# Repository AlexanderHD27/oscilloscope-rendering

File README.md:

# Oscilloscope Drawing

A device that draws on an oscilloscope.

## Introduction
Drawing on analog oscilloscope is almost a classic in the electronics/microcontroller community now.
This is done by setting the scope to XY-Mode and then controlling the X/Y-deflection of the electron-beam. My Scope has no Z-Channel. I cannot control the intensity of beam (or switches off) by voltage yet

This Project is my shot at this. I use custom hardware (build on perf-board) to archive this goal. I have build
a 2-Channel 16bit DAC with an refresh rate of around 1 MSample per second. Further more a usb-interface + driver shall be developed.

My current todo list can be found [here](TODO.md)

### Hardware

Everything is solder onto pref-boards an connected via pin-headers and jumpers

(Diagram of the System-Hardware components)

The DACs are R-2R-Ladder DAC on a made custom PCB. The Input-Bits are feed from Octal-D-Latches ([74HC573](https://www.reichelt.de/oktal-d-type-latch-3-state-2--6-v-dil-20-74hc-573-p3264.html?search=74HC573)) in combination with some other logic ICs to reduce pin usage on the RPi Pico. Data sent via a 8-bit a parallel Bus to

<br>

At 1 MHz Square Wave, the analog output signal quality is significantly degraded. Testing revealed that probably R-2R_Ladder DAC is the weak link and needs further improvement. I currently use R = 11kOhm.

Yellow: X-Channel, Blue: Y-Channel, Magenta: Digital Input Signal to the DAC. (Yellow and Blue are coupled to AC, they usually to remove the 2.5V offset)

For testing the optics I did use a Hameg MH 312 Oscilloscope (I got this one used from Kleinanzeigen, so its already falling apart: semi-broken Coupling-switch, not being able focus the beam correctly, X-Pos nob falling off all the time)

### Further Components
- [Firmware](./firmware/README.md): Documentation is done by [doxygen](https://www.mintcalc.com/projects/osci-rendering/docs/index.html)

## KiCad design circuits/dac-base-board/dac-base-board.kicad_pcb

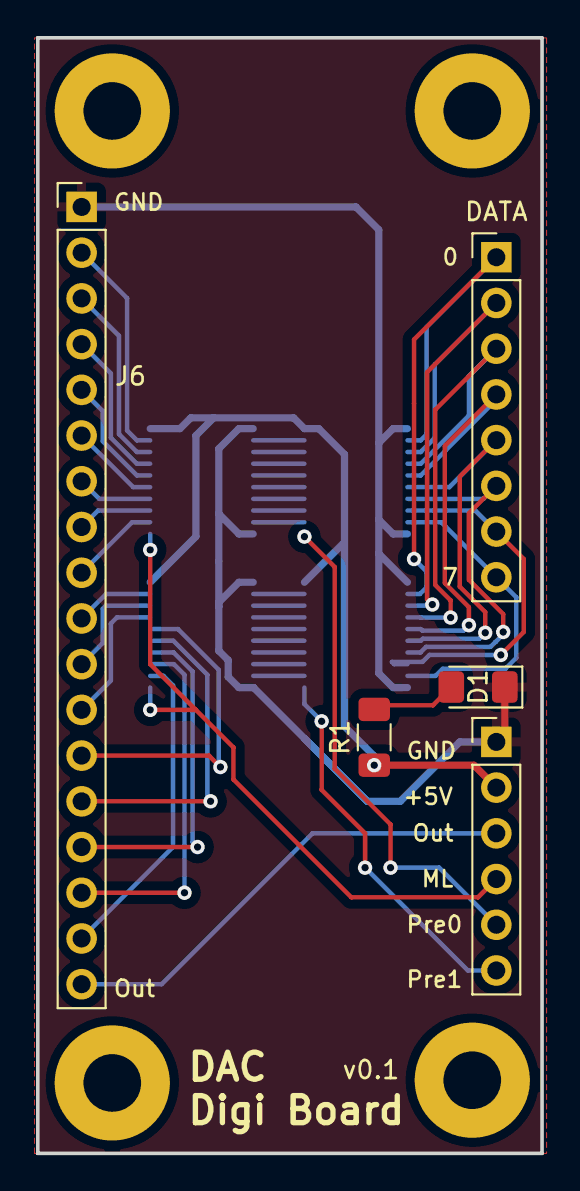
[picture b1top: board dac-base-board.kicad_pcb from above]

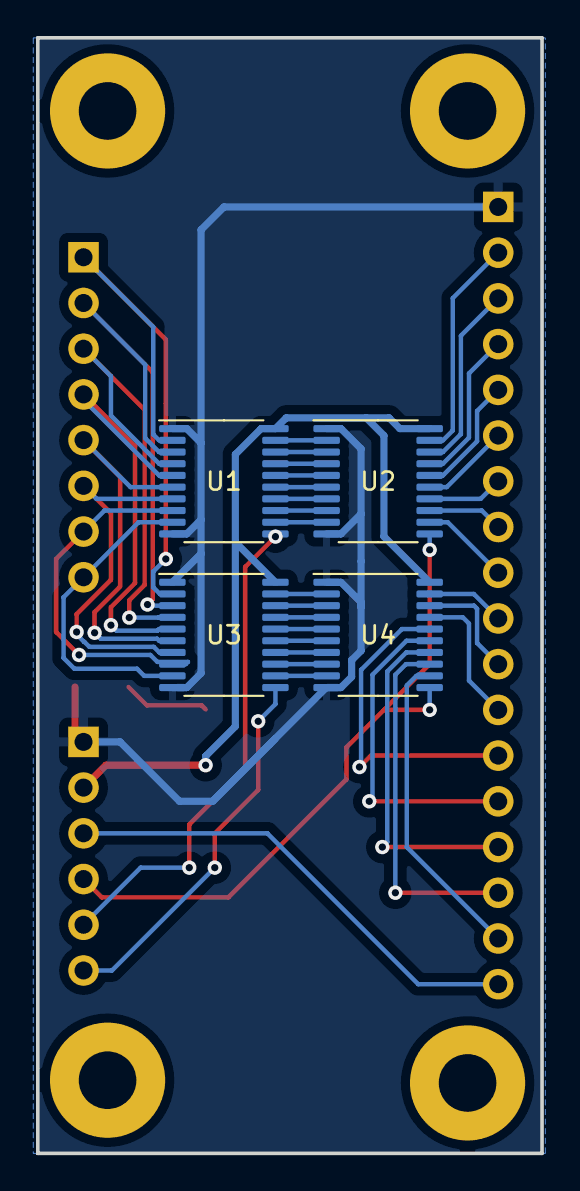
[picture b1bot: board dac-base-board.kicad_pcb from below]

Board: 2 copper layers, 28.0 x 62.0 mm, 12 parts (4 on the bottom side), 47 nets.

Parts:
D1: LED; LED_1206_3216Metric_Pad1.42x1.75mm_HandSolder
DATA: Data; PinHeader_1x08_P2.54mm_Vertical
J1: Conn; PinHeader_1x06_P2.54mm_Vertical
J6: DAC X; PinHeader_1x18_P2.54mm_Vertical
R1: 220; R_1206_3216Metric_Pad1.30x1.75mm_HandSolder
REF: MountingHole_3.2mm_M3_Pad
REF#2, REF#3: MountingHole_3.2mm_M3_Pad
U1, U2, U3, U4: 74LS573; TSSOP-20_4.4x6.5mm_P0.65mm

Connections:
+5V: J1.2, R1.2, U1.20 (VCC), U2.20 (VCC), U3.20 (VCC), U4.20 (VCC)
/D0: DATA.1, U1.2 (D0), U3.2 (D0)
/D1: DATA.2, U1.3 (D1), U3.3 (D1)
/D2: DATA.3, U1.4 (D2), U3.4 (D2)
/D3: DATA.4, U1.5 (D3), U3.5 (D3)
/D4: DATA.5, U1.6 (D4), U3.6 (D4)
/D5: DATA.6, U1.7 (D5), U3.7 (D5)
/D6: DATA.7, U1.8 (D6), U3.8 (D6)
/D7: DATA.8, U1.9 (D7), U3.9 (D7)
/DAC_D0: J6.2, U2.19 (Q0)
/DAC_D1: J6.3, U2.18 (Q1)
/DAC_D2: J6.4, U2.17 (Q2)
/DAC_D3: J6.5, U2.16 (Q3)
/DAC_D4: J6.6, U2.15 (Q4)
/DAC_D5: J6.7, U2.14 (Q5)
/DAC_D6: J6.8, U2.13 (Q6)
/DAC_D7: J6.9, U2.12 (Q7)
/DAC_D8: J6.10, U4.19 (Q0)
/DAC_D9: J6.11, U4.18 (Q1)
/DAC_D10: J6.12, U4.17 (Q2)
/DAC_D11: J6.13, U4.16 (Q3)
/DAC_D12: J6.14, U4.15 (Q4)
/DAC_D13: J6.15, U4.14 (Q5)
/DAC_D14: J6.16, U4.13 (Q6)
/DAC_D15: J6.17, U4.12 (Q7)
/Master_Load: J1.4, U2.11 (Load), U4.11 (Load)
/OUT: J1.3, J6.18
/Pre0: J1.5, U1.11 (Load)
/Pre1: J1.6, U3.11 (Load)
GND: D1.1 (K), J1.1, J6.1, U1.1 (OE), U1.10 (GND), U2.1 (OE), U2.10 (GND), U3.1 (OE), U3.10 (GND), U4.1 (OE), U4.10 (GND)
unnamed: D1.2 (A), R1.1
unnamed: U1.19 (Q0), U2.2 (D0)
unnamed: U1.18 (Q1), U2.3 (D1)
unnamed: U1.17 (Q2), U2.4 (D2)
unnamed: U1.16 (Q3), U2.5 (D3)
unnamed: U1.15 (Q4), U2.6 (D4)
unnamed: U1.14 (Q5), U2.7 (D5)
unnamed: U1.13 (Q6), U2.8 (D6)
unnamed: U1.12 (Q7), U2.9 (D7)
unnamed: U3.19 (Q0), U4.2 (D0)
unnamed: U3.18 (Q1), U4.3 (D1)
unnamed: U3.17 (Q2), U4.4 (D2)
unnamed: U3.16 (Q3), U4.5 (D3)
unnamed: U3.15 (Q4), U4.6 (D4)
unnamed: U3.14 (Q5), U4.7 (D5)
unnamed: U3.13 (Q6), U4.8 (D6)
unnamed: U3.12 (Q7), U4.9 (D7)

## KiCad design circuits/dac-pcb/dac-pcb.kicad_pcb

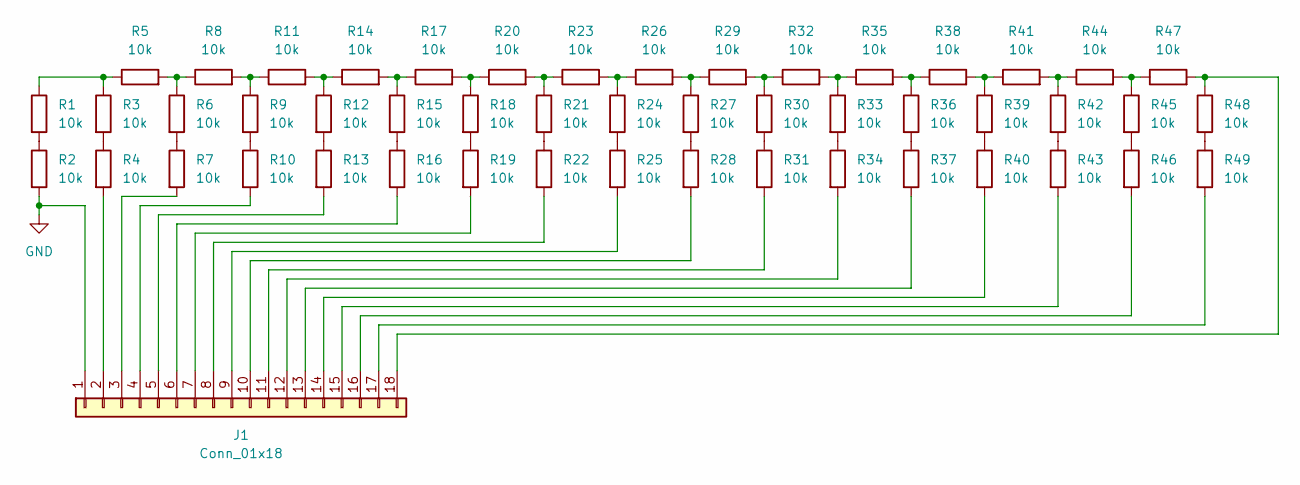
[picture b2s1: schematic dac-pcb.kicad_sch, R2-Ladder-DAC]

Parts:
J1: Conn_01x18; PinHeader_1x18_P2.54mm_Horizontal
R1, R2, R3, R4, R5, R6, R7, R8, R9, R10, R11, R12, R13, R14, R15, R16, R17, R18, R19, R20, R21, R22, R23, R24, R25, R26, R27, R28, R29, R30, R31, R32, R33, R34, R35, R36, R37, R38, R39, R40, R41, R42, R43, R44, R45, R46, R47, R48, R49: 10k; R_1206_3216Metric

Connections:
GND: J1.1, R2.2
unnamed: J1.2, R4.2
unnamed: J1.3, R7.2
unnamed: J1.4, R10.2
unnamed: J1.5, R13.2
unnamed: J1.6, R16.2
unnamed: J1.7, R19.2
unnamed: J1.8, R22.2
unnamed: J1.9, R25.2
unnamed: J1.10, R28.2
unnamed: J1.11, R31.2
unnamed: J1.12, R34.2
unnamed: J1.13, R37.2
unnamed: J1.14, R40.2
unnamed: J1.15, R43.2
unnamed: J1.16, R46.2
unnamed: J1.17, R49.2
unnamed: J1.18, R47.2, R48.1
unnamed: R1.1, R3.1, R5.1
unnamed: R1.2, R2.1
unnamed: R3.2, R4.1
unnamed: R5.2, R6.1, R8.1
unnamed: R6.2, R7.1
unnamed: R9.2, R10.1
unnamed: R8.2, R9.1, R11.1
unnamed: R11.2, R12.1, R14.1
unnamed: R12.2, R13.1
unnamed: R14.2, R15.1, R17.1
unnamed: R15.2, R16.1
unnamed: R17.2, R18.1, R20.1
unnamed: R18.2, R19.1
unnamed: R20.2, R21.1, R23.1
unnamed: R21.2, R22.1
unnamed: R23.2, R24.1, R26.1
unnamed: R24.2, R25.1
unnamed: R26.2, R27.1, R29.1
unnamed: R27.2, R28.1
unnamed: R29.2, R30.1, R32.1
unnamed: R30.2, R31.1
unnamed: R32.2, R33.1, R35.1
unnamed: R33.2, R34.1
unnamed: R35.2, R36.1, R38.1
unnamed: R36.2, R37.1
unnamed: R38.2, R39.1, R41.1
unnamed: R39.2, R40.1
unnamed: R41.2, R42.1, R44.1
unnamed: R42.2, R43.1
unnamed: R44.2, R45.1, R47.1
unnamed: R45.2, R46.1
unnamed: R48.2, R49.1

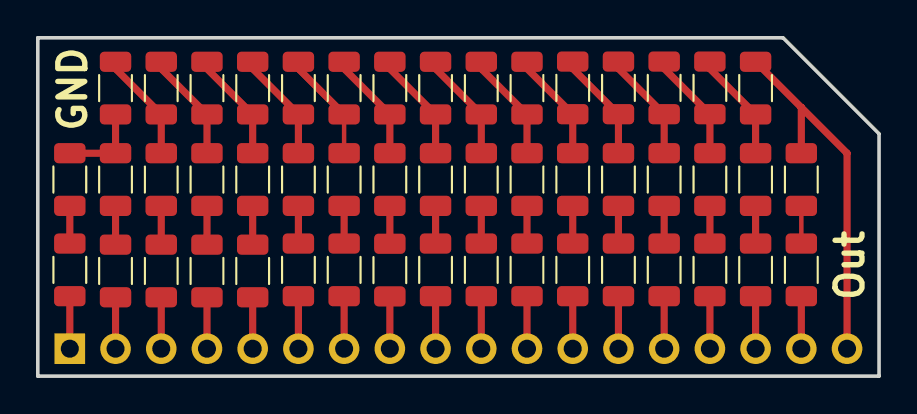
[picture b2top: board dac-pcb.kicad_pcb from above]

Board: 2 copper layers, 46.7 x 18.8 mm, 50 parts (1 on the bottom side), 50 nets.

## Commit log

2024-02-09 Added README + some doc images + SystemSchematic
2024-02-09 Added basic firmware to repo
2024-02-09 Added DAC-pcb
2024-02-09 Added PCB Manfucaturer to README
2024-02-10 Added USB test file/project to CMake & DevEnv
2024-02-10 Add tinyusb
2024-02-10 removed symlinks of example_auto_set_url.cmake and pico_sdk_import.cmake
2024-02-10 Update README.md with link to dac-pcb prod-file
2024-02-10 Fixed missing label in HardwareSystemDiagram
2024-02-10 Change PICO sdk to workspace-local sdk
2024-02-10 Got Pico SDK example of USB to work
2024-02-10 Cleaned up DAC code and separated it into folder
2024-02-11 Implemented basic generators
2024-02-11 Added squares.jpeg
2024-02-11 Update README.md with a small todo list
2024-02-11 Create Flow-Chart for Job System
2024-02-11 Fixed Problem with second core not starting after reset via openocd
2024-02-12 Added FreeRTOS to project
2024-02-12 Created flow-chart for new queue-based dataflow
2024-02-12 FlowChart: Updated some stuff and added task names
2024-02-12 Implemented queue base system
2024-02-12 Found Deadlock Issue
2024-02-12 Fixed deadlock issue by removing jobs queue and implemented frame-repeat
2024-02-12 Change buffer miss to check next cycle (instead of next frame repeat cycle)
2024-02-12 Reorganized Docs and updated README
2024-02-12 Update README.md inserted missing new line
2024-02-12 Create Instruction Parsing + Generation of NONE, CONST and LINE
2024-02-13 Implement cubic generation for floats and fixpoint
2024-02-13 Fixed bug in parameter reading
2024-02-13 Updated FreeRTOS-Kernel
2024-02-13 Implemented Qubic Curves
2024-02-14 Implemented Fixpoint taylor series for sin
2024-02-14 Fixed skipped samples by Invalid Offset
2024-02-14 built small sin&cos demo
2024-02-14 Added Demo of rendering sine
2024-02-14 Squashed commit of the following:
    commit 72b70e328290417968875a4158c1d6cbc331ddba
    Author: alexander <alexander@hal>
    Date: Wed Feb 14 22:44:02 2024 +0100
    Added Demo of rendering sine
    commit 6b187587fa563b0e1b60a151fd09fe397362b101
    Author: alexander <alexander@hal>
2024-02-15 Moved some stuff around and renamed variables to fit naming convention
2024-02-15 Added doxygen docs
2024-02-15 Added Wiring Drawing
2024-02-15 Added Doxygen Main Page + Renamed some names to fit standard
2024-02-15 Updated TODO.md
2024-02-15 Added KiCad Lib for RPi Pico Symbol
2024-02-16 Created Jenkinsfile
2024-02-16 Test Commit: Trigger webhook, pls
2024-02-16 Created Build Container
2024-02-16 Change invalid submodule path
2024-02-16 Create Pipeline for building docs and firmware
2024-02-16 parallized build step
2024-02-16 Added auto-publish stage
2024-02-16 Fixed issue with jenkinsfile
2024-02-16 Added stashes and unstash to Jenkins file
2024-02-16 Added clean before publish
2024-02-16 Fixed Issue: only stashed files not subdirectories
2024-02-16 Squashed commit of the following:
    commit a94d0bf17ec5a08377fb8872f7ad4f6ed2f576aa
    Merge: 5e9ef28 7bf5eda
    Author: alexander <alexander@hal>
    Date: Fri Feb 16 23:17:03 2024 +0100
    Merge branch 'feature-add-jenkins' of github.com:AlexanderHD27/oscilloscope-rendering into feature-add-jenkins
    commit 5e9ef286059d3a9ea7164fecc8cb96002f096ec3
2024-02-16 Added Link to doc to READMEs
2024-02-16 In Jenkinsfile, set correct branch
2024-02-16 Added link to build binary form build server
2024-02-17 setup base structure
2024-02-18 Aktualisieren von README.md
2024-02-18 Got USB cdc to work, no tinyUSB docs :/
2024-02-18 Change RTOS to SMP and pinned processing to core1, to not overload the pico
2024-02-18 Moved Config Headers to separate folder
2024-02-18 Added doxygen-docs for usb stuff
2024-02-18 Implemented Instruction transmission via USB \0/
2024-02-18 Added Interrupt endpoint to get response, when finished writing
2024-02-18 updated TODO List
2024-02-18 Squashed commit of the following:
    commit 475b533dc990b1b307ecd055ab3a6463d4959759
    Author: alexander <alexander@hal>
    Date: Mon Feb 19 00:20:53 2024 +0100
    updated TODO List
    commit 11cf20766dc8c532523d47bdbed6e1dc29e11dcb
    Author: alexander <alexander@hal>
2024-02-19 Removed Tiny USB Implementation
2024-02-20 Added new line
2024-02-21 started building lowlevel implementation
2024-02-21 Optimized Instruction through put
2024-02-21 Added Clustering of instructions (in crease ~30 ms per Buffer)
2024-02-28 something
2024-04-20 Added baseboard
